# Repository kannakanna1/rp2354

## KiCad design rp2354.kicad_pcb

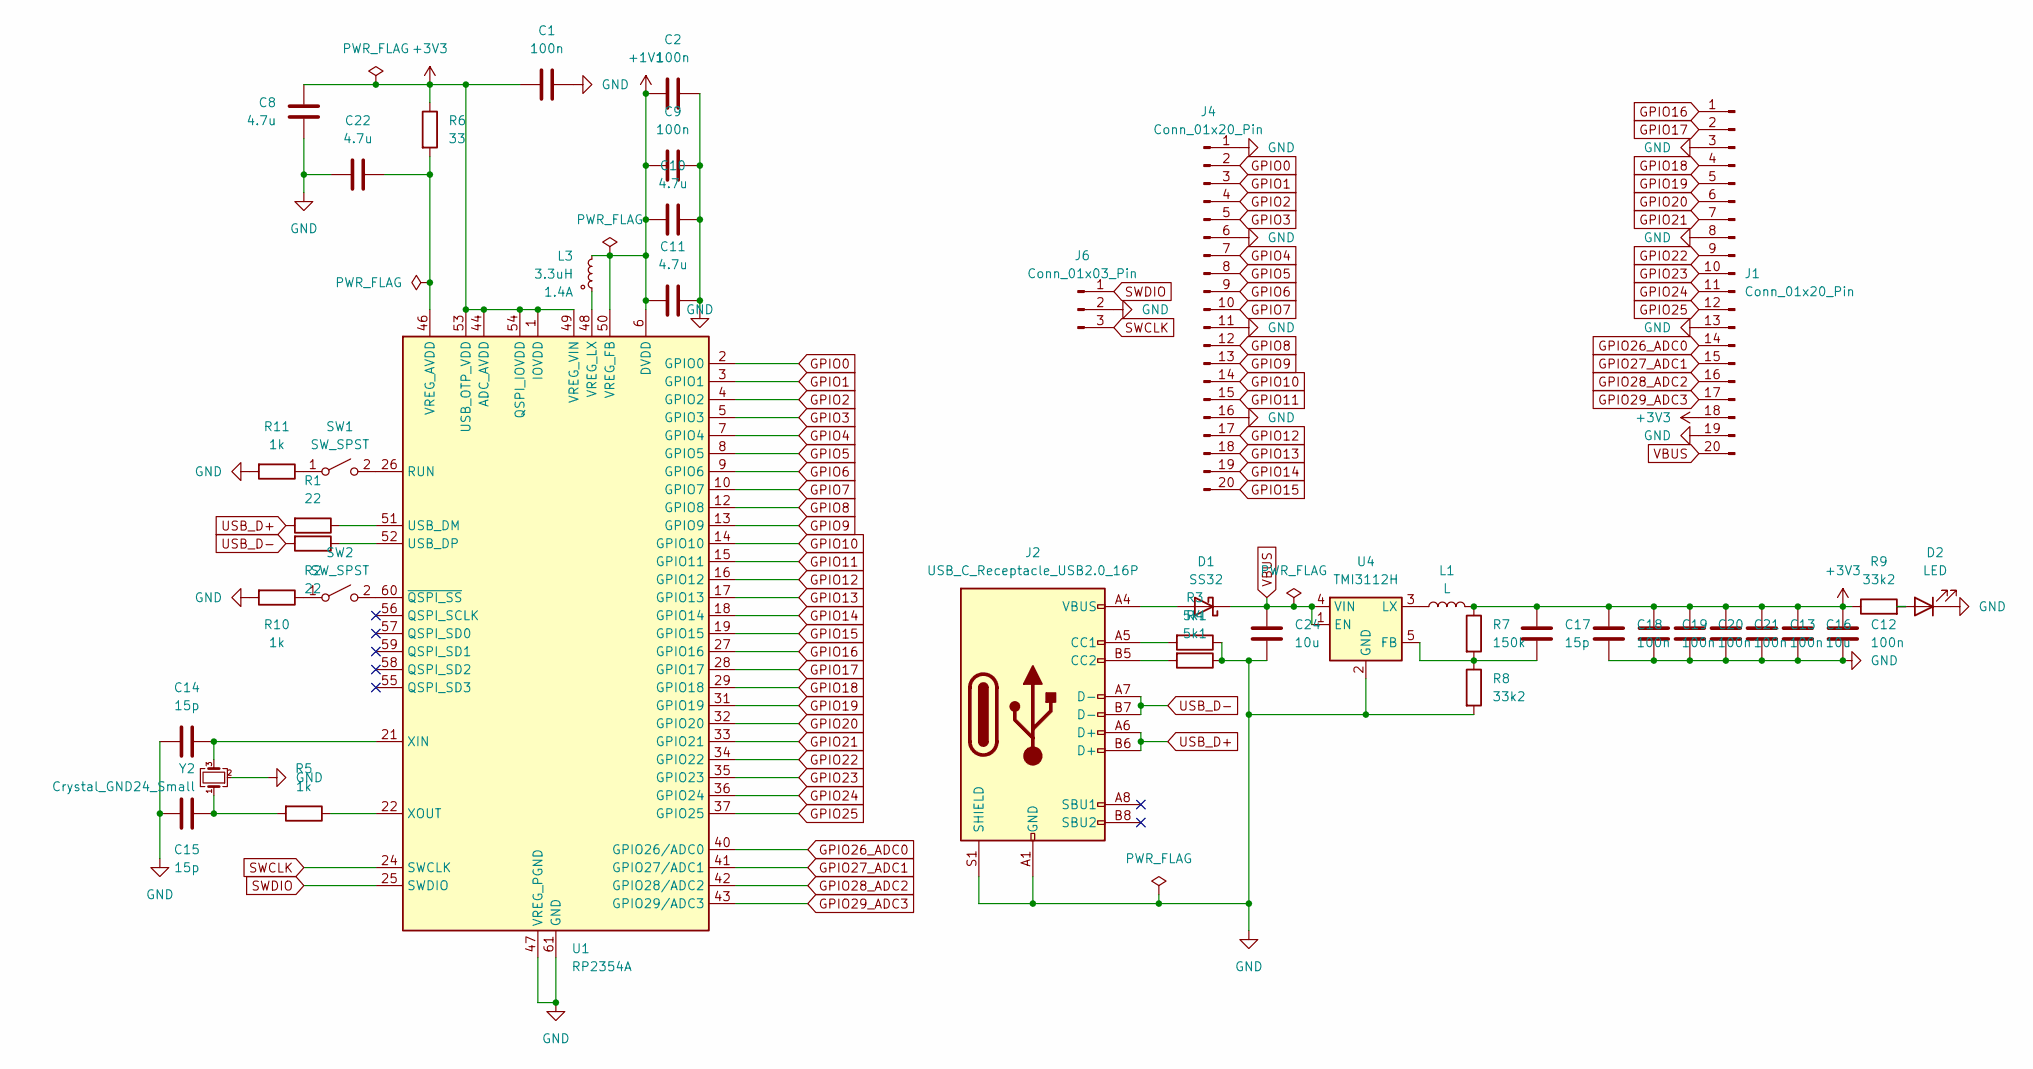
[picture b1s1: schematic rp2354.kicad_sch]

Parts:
C1, C2, C9, C12, C13, C18, C19, C20, C21: 100n; C_0603_1608Metric
C8, C10, C11, C22: 4.7u; C_0603_1608Metric
C14, C15, C17: 15p; C_0603_1608Metric
C16, C24: 10u; C_0603_1608Metric
D1: SS32; D_SMA
D2: LED; LED_0603_1608Metric
J1, J4: Conn_01x20_Pin; PinHeader_1x20_P2.54mm_Vertical
J2: USB_C_Receptacle_USB2.0_16P; USB_C_Receptacle_GCT_USB4105-xx-A_16P_TopMnt_Horizontal
J6: Conn_01x03_Pin
L1: L; L_1008_2520Metric
L3: 3.3uH; 0806_Polarized
R1, R2: 22; R_0603_1608Metric
R3, R4: 5k1; R_0603_1608Metric
R5, R10, R11: 1k; R_0603_1608Metric
R6: 33; R_0603_1608Metric
R7: 150k; R_0603_1608Metric
R8, R9: 33k2; R_0603_1608Metric
SW1, SW2: SW_SPST; SW_Push_1P1T_NO_Vertical_Wuerth_434133025816
U1: RP2354A; QFN-60-1EP_7x7mm_P0.4mm_EP3.4x3.4mm
U4: TMI3112H; SOT-23-5
Y2: Crystal_GND24_Small; Crystal_SMD_3225-4Pin_3.2x2.5mm

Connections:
+1V1: C2.1, C9.1, C10.1, C11.1, L3.2, U1.6 (DVDD), U1.23 (DVDD), U1.39 (DVDD), U1.50 (VREG_FB)
+3V3: C1.1, C8.1, C12.1, C13.1, C16.1, C17.1, C18.1, C19.1, C20.1, C21.1, J1.18, L1.2, R6.1, R7.1, R9.1, U1.1 (IOVDD), U1.11 (IOVDD), U1.20 (IOVDD), U1.30 (IOVDD), U1.38 (IOVDD), U1.44 (ADC_AVDD), U1.45 (IOVDD), U1.49 (VREG_VIN), U1.53 (USB_OTP_VDD), U1.54 (QSPI_IOVDD)
GND: C1.2, C2.2, C8.2, C9.2, C10.2, C11.2, C12.2, C13.2, C14.2, C15.1, C16.2, C18.2, C19.2, C20.2, C21.2, C22.1, C24.2, D2.1 (K), J1.3, J1.8, J1.13, J1.19, J2.A1 (GND), J2.A12 (GND), J2.B1 (GND), J2.B12 (GND), J2.S1 (SHIELD), J4.1, J4.6, J4.11, J4.16, J6.2, R3.1, R4.1, R8.2, R10.2, R11.2, U1.47 (VREG_PGND), U1.61 (GND), U4.2 (GND), Y2.2 (G), Y2.4 (G)
GPIO0: J4.2, U1.2 (GPIO0)
GPIO1: J4.3, U1.3 (GPIO1)
GPIO2: J4.4, U1.4 (GPIO2)
GPIO3: J4.5, U1.5 (GPIO3)
GPIO4: J4.7, U1.7 (GPIO4)
GPIO5: J4.8, U1.8 (GPIO5)
GPIO6: J4.9, U1.9 (GPIO6)
GPIO7: J4.10, U1.10 (GPIO7)
GPIO8: J4.12, U1.12 (GPIO8)
GPIO9: J4.13, U1.13 (GPIO9)
GPIO10: J4.14, U1.14 (GPIO10)
GPIO11: J4.15, U1.15 (GPIO11)
GPIO12: J4.17, U1.16 (GPIO12)
GPIO13: J4.18, U1.17 (GPIO13)
GPIO14: J4.19, U1.18 (GPIO14)
GPIO15: J4.20, U1.19 (GPIO15)
GPIO16: J1.1, U1.27 (GPIO16)
GPIO17: J1.2, U1.28 (GPIO17)
GPIO18: J1.4, U1.29 (GPIO18)
GPIO19: J1.5, U1.31 (GPIO19)
GPIO20: J1.6, U1.32 (GPIO20)
GPIO21: J1.7, U1.33 (GPIO21)
GPIO22: J1.9, U1.34 (GPIO22)
GPIO23: J1.10, U1.35 (GPIO23)
GPIO24: J1.11, U1.36 (GPIO24)
GPIO25: J1.12, U1.37 (GPIO25)
GPIO26_ADC0: J1.14, U1.40 (GPIO26/ADC0)
GPIO27_ADC1: J1.15, U1.41 (GPIO27/ADC1)
GPIO28_ADC2: J1.16, U1.42 (GPIO28/ADC2)
GPIO29_ADC3: J1.17, U1.43 (GPIO29/ADC3)
unnamed: C15.2, R5.2, Y2.1
unnamed: D1.2 (A), J2.A4 (VBUS), J2.A9 (VBUS), J2.B4 (VBUS), J2.B9 (VBUS)
unnamed: D2.2 (A), R9.2
unnamed: J2.A5 (CC1), R3.2
unnamed: J2.B5 (CC2), R4.2
unnamed: R11.1, SW1.1 (A)
unnamed: SW1.2 (B), U1.26 (RUN)
unnamed: R10.1, SW2.1 (A)
unnamed: SW2.2 (B), U1.60 (~QSPI_SS)
unnamed: R1.1, U1.51 (USB_DM)
unnamed: R2.1, U1.52 (USB_DP)
unnamed: C22.2, R6.2, U1.46 (VREG_AVDD)
unnamed: L3.1, U1.48 (VREG_LX)
unnamed: C14.1, U1.21 (XIN), Y2.3
unnamed: R5.1, U1.22 (XOUT)
unnamed: C17.2, R7.2, R8.1, U4.5 (FB)
unnamed: L1.1, U4.3 (LX)
SWCLK: J6.3, U1.24 (SWCLK)
SWDIO: J6.1, U1.25 (SWDIO)
USB_D+: J2.A6 (D+), J2.B6 (D+), R1.2
USB_D-: J2.A7 (D-), J2.B7 (D-), R2.2
VBUS: C24.1, D1.1 (K), J1.20, U4.1 (EN), U4.4 (VIN)

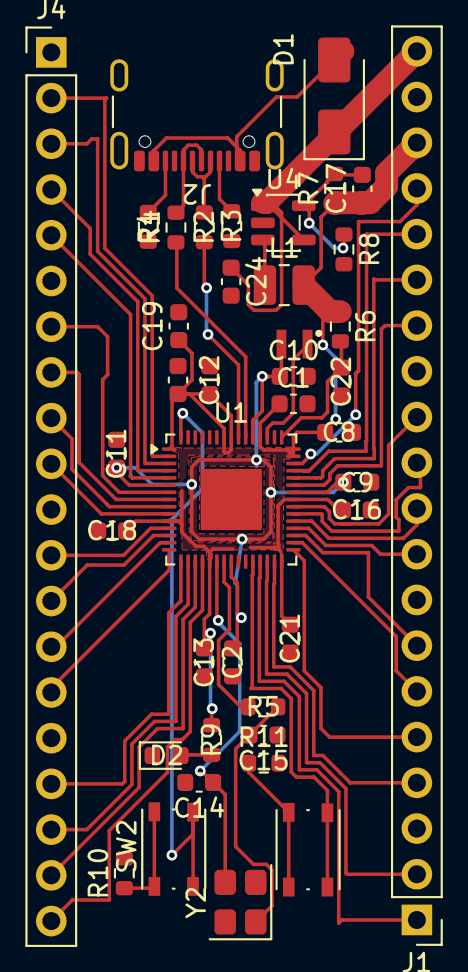
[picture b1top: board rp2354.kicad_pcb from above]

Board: 2 copper layers, 41 parts (0 on the bottom side), 53 nets.
